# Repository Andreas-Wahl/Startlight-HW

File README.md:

# STARTAMPEL "Bären(n)keller" 🚦

## Project Overview 🏎️

In a private cellar bar that has been in existence for over two generations, originally named "Bärenkeller," a CARRERA® digital 132 racetrack was set up, and the first races were held. This quickly gained popularity among friends and acquaintances. As a result, the racetrack was gradually expanded, and possible extensions were discussed.

The idea of creating a custom starting light emerged because the original CARRERA® Startlight (30354) could not bridge three lanes (two lanes + pit lane). Additionally, the custom STARTAMPEL should not only display the start sequence with red lights but also indicate the race operation with green LEDs, the safety car/pace car operation, and a false start.

The idea was quickly taken up, the data signal was analyzed with an oscilloscope and data logger, and the development of hardware, software, and housing design was initiated.

In reference to the "Bärenkeller," which was renamed "Bären(n)keller" due to the expansion of the CARRERA® digital 132 racetrack, the custom starting light was also named "STARTAMPEL 'Bären(n)keller'."

The STARTAMPEL "Bären(n)keller" was so well received that the developer decided to produce a small quantity as "prototypes" and make the development available for non-commercial use.

## Licensing 📜

- **Electronics and Housing Design**: Released under the Creative Commons Attribution-NonCommercial-ShareAlike 4.0 International License (CC BY-NC-SA 4.0).
- **Software**: Released under the GNU Affero General Public License, Version 3.0 (AGPL-3.0).

## Repository Contents 📂

- **Schematic**: The complete schematic for the STARTAMPEL "Bären(n)keller".
- **PCB Layout**: The PCB layout files for the project.
- **Hardware Documentation**: Detailed documentation on the hardware development and usage.

## Getting Started 🚀

To get started with the project, clone the repository and follow the instructions in the documentation to set up the hardware and software.

```bash
git clone https://github.com/Andreas-Wahl/Startlight-HW.git

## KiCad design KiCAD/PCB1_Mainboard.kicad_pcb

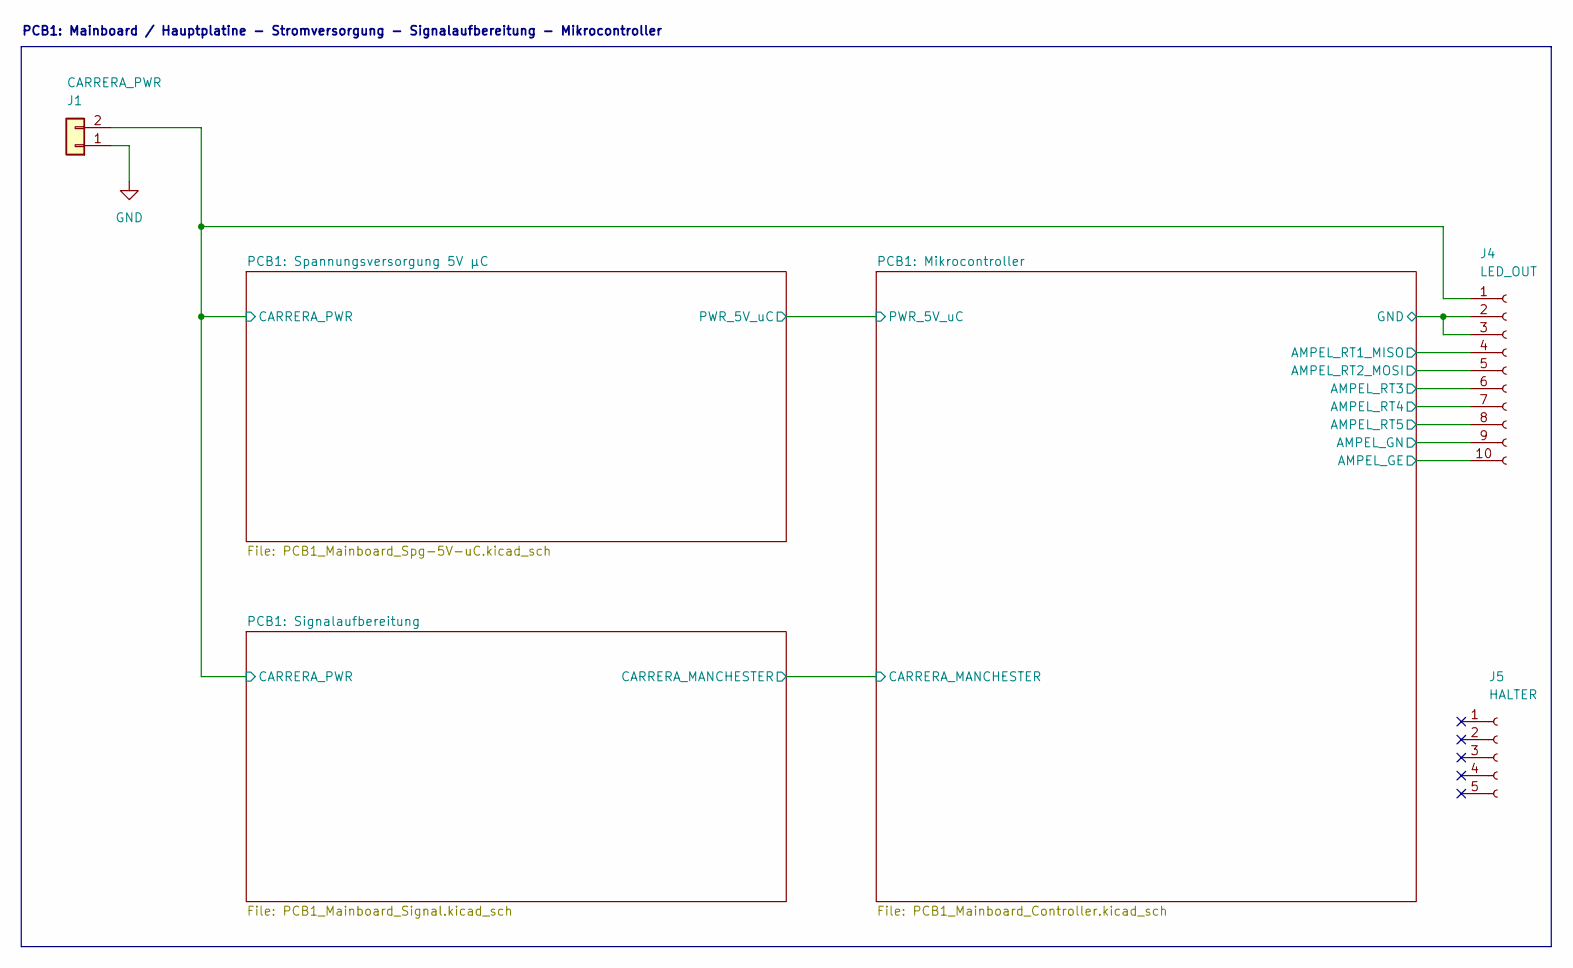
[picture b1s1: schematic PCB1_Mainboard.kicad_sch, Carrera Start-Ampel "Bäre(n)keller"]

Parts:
J1: CARRERA_PWR; JST_XH_B2B-XH-A_1x02_P2.50mm_Vertical
J4: LED_OUT; PinSocket_1x10_P2.54mm_Vertical
J5: HALTER; PinSocket_1x05_P2.54mm_Vertical

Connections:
/PCB1: Mikrocontroller/AMPEL_GE: J4.10; also elsewhere on the board
/PCB1: Mikrocontroller/AMPEL_GN: J4.9; also elsewhere on the board
/PCB1: Mikrocontroller/AMPEL_RT1_MISO: J4.4; also elsewhere on the board
/PCB1: Mikrocontroller/AMPEL_RT2_MOSI: J4.5; also elsewhere on the board
/PCB1: Mikrocontroller/AMPEL_RT3: J4.6; also elsewhere on the board
/PCB1: Mikrocontroller/AMPEL_RT4: J4.7; also elsewhere on the board
/PCB1: Mikrocontroller/AMPEL_RT5: J4.8; also elsewhere on the board
/PCB1: Signalaufbereitung/CARRERA_PWR: J1.2, J4.1; also elsewhere on the board
GND: J1.1, J4.2, J4.3; also elsewhere on the board

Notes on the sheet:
PCB1: Mainboard / Hauptplatine - Stromversorgung - Signalaufbereitung - Mikrocontroller

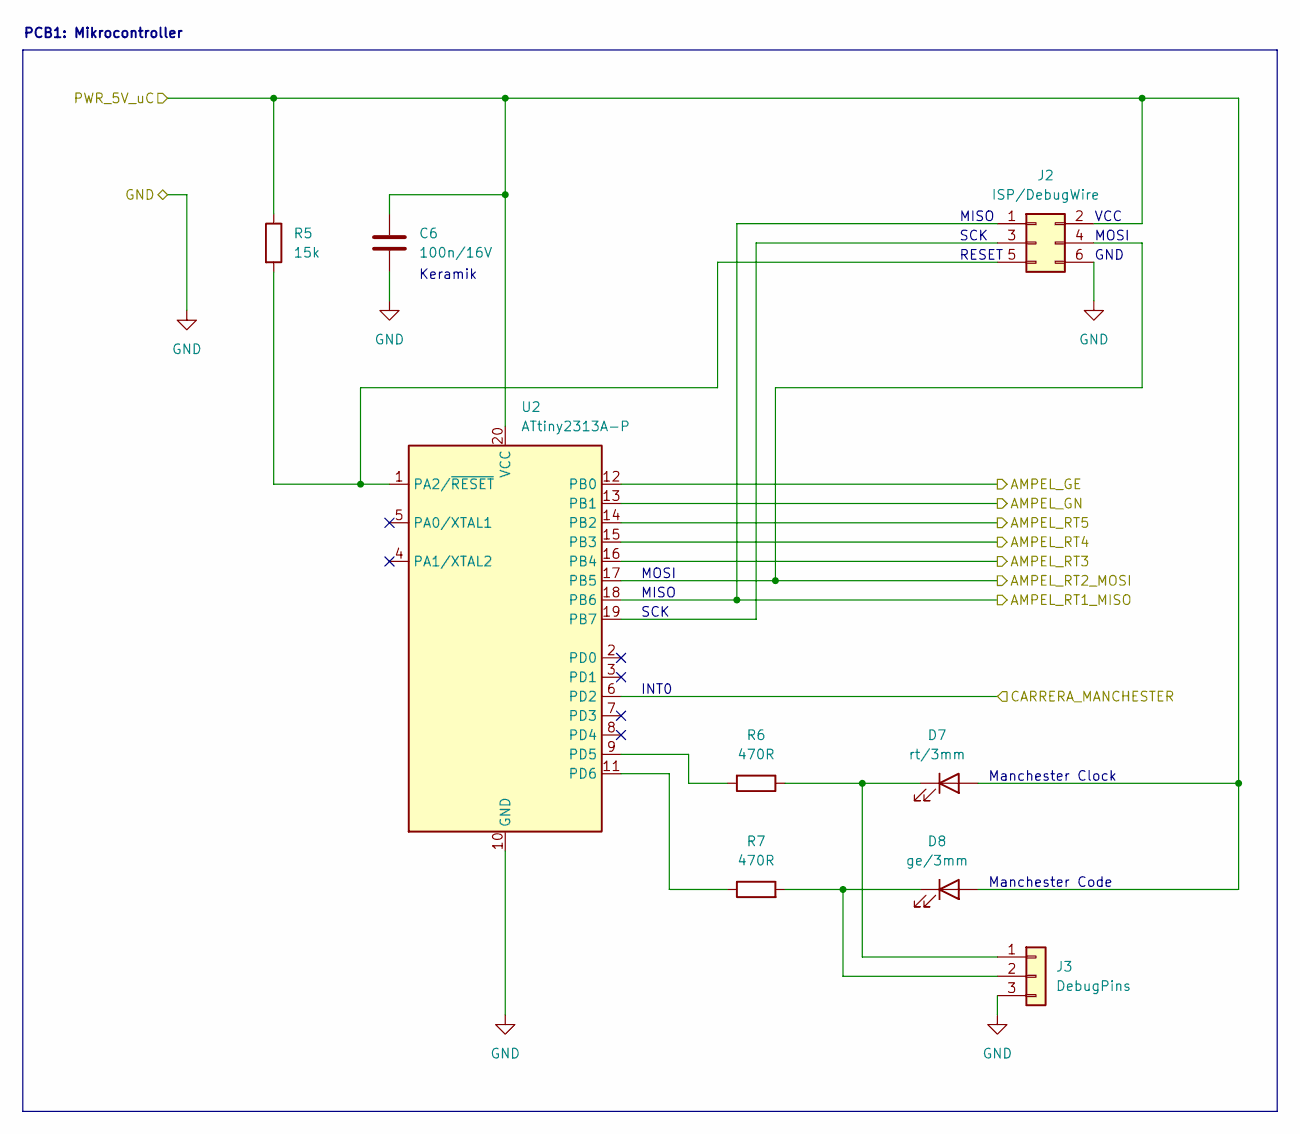
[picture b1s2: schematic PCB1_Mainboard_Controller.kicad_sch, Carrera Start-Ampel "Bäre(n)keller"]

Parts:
C6: 100n/16V; C_Disc_D5.0mm_W2.5mm_P5.00mm
D7: rt/3mm; LED_D3.0mm-rd
D8: ge/3mm; LED_D3.0mm-ye
J2: ISP/DebugWire; PinHeader_2x03_P2.54mm_Horizontal
J3: DebugPins; PinHeader_1x03_P2.54mm_Horizontal
R5: 15k; R_Axial_DIN0207_L6.3mm_D2.5mm_P10.16mm_Horizontal
R6, R7: 470R; R_Axial_DIN0207_L6.3mm_D2.5mm_P10.16mm_Horizontal
U2: ATtiny2313A-P; DIP-20_W7.62mm

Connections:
/PCB1: Mikrocontroller/AMPEL_GE: U2.12 (PB0); also elsewhere on the board
/PCB1: Mikrocontroller/AMPEL_GN: U2.13 (PB1); also elsewhere on the board
/PCB1: Mikrocontroller/AMPEL_RT1_MISO: J2.1, U2.18 (PB6); also elsewhere on the board
/PCB1: Mikrocontroller/AMPEL_RT2_MOSI: J2.4, U2.17 (PB5); also elsewhere on the board
/PCB1: Mikrocontroller/AMPEL_RT3: U2.16 (PB4); also elsewhere on the board
/PCB1: Mikrocontroller/AMPEL_RT4: U2.15 (PB3); also elsewhere on the board
/PCB1: Mikrocontroller/AMPEL_RT5: U2.14 (PB2); also elsewhere on the board
/PCB1: Mikrocontroller/CARRERA_MANCHESTER: U2.6 (PD2); also elsewhere on the board
/PCB1: Mikrocontroller/PWR_5V_uC: C6.1, D7.2 (A), D8.2 (A), J2.2, R5.1, U2.20 (VCC); also elsewhere on the board
GND: C6.2, J2.6, J3.3, U2.10 (GND); also elsewhere on the board
unnamed: D7.1 (K), J3.1, R6.1
unnamed: D8.1 (K), J3.2, R7.2
unnamed: J2.3, U2.19 (PB7)
unnamed: J2.5, R5.2, U2.1 (PA2/~RESET)
unnamed: R6.2, U2.9 (PD5)
unnamed: R7.1, U2.11 (PD6)

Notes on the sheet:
SCK
MISO
Manchester Clock
PCB1: Mikrocontroller
Keramik
GND
Manchester Code
MOSI
RESET
INT0
VCC

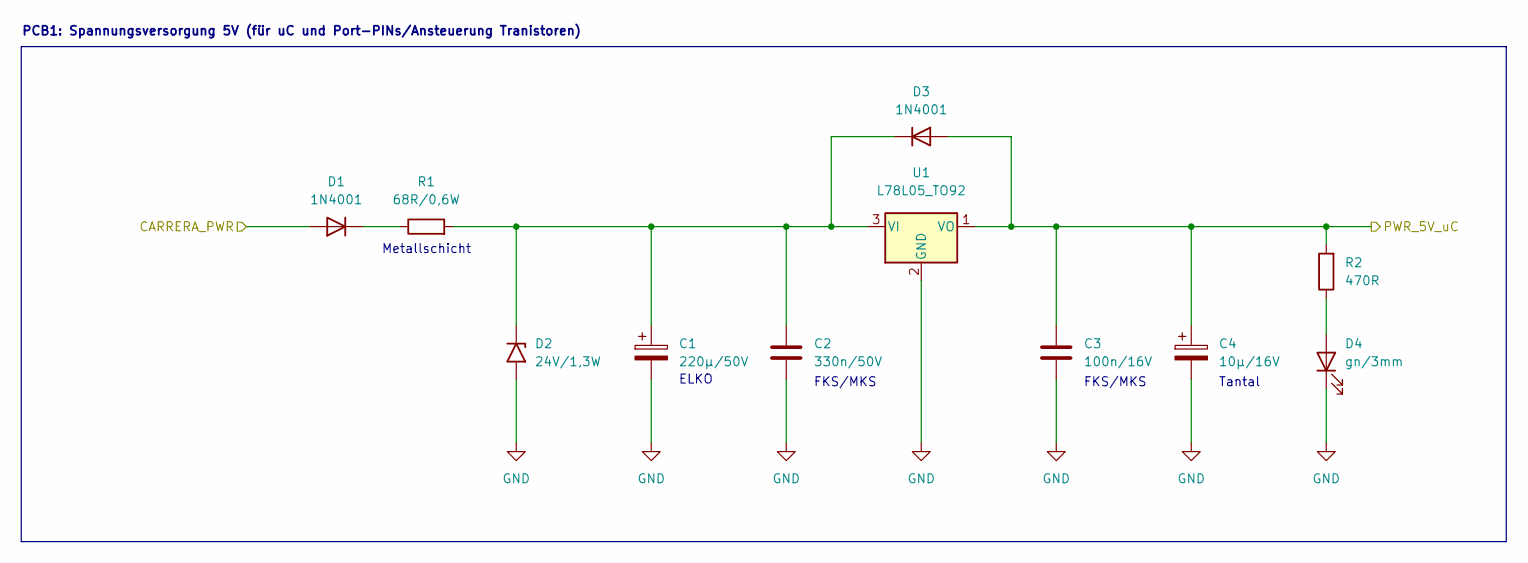
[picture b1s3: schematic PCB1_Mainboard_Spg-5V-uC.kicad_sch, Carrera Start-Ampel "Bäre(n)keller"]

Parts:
C1: 220µ/50V; CP_Radial_D10.0mm_P5.00mm
C2: 330n/50V; C_Rect_L7.2mm_W2.5mm_P5.00mm_FKS2_FKP2_MKS2_MKP2
C3: 100n/16V; C_Rect_L7.2mm_W2.5mm_P5.00mm_FKS2_FKP2_MKS2_MKP2
C4: 10µ/16V; CP_Radial_Tantal_D5.5mm_P2.50mm
D1, D3: 1N4001; D_DO-41_SOD81_P10.16mm_Horizontal
D2: 24V/1,3W; D_DO-41_SOD81_P10.16mm_Horizontal
D4: gn/3mm; LED_D3.0mm-gn
R1: 68R/0,6W; R_Axial_DIN0207_L6.3mm_D2.5mm_P10.16mm_Horizontal
R2: 470R; R_Axial_DIN0207_L6.3mm_D2.5mm_P10.16mm_Horizontal
U1: L78L05_TO92; TO-92_Wide

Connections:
/PCB1: Mikrocontroller/PWR_5V_uC: C3.1, C4.1, D3.2 (A), R2.2, U1.1 (VO); also elsewhere on the board
/PCB1: Signalaufbereitung/CARRERA_PWR: D1.2 (A); also elsewhere on the board
GND: C1.2, C2.2, C3.2, C4.2, D2.2 (A2), D4.1 (K), U1.2 (GND); also elsewhere on the board
unnamed: D1.1 (K), R1.1
unnamed: C1.1, C2.1, D2.1 (A1), D3.1 (K), R1.2, U1.3 (VI)
unnamed: D4.2 (A), R2.1

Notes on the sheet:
Tantal
Metallschicht
ELKO
PCB1: Spannungsversorgung 5V (für uC und Port-PINs/Ansteuerung Tranistoren)
FKS/MKS

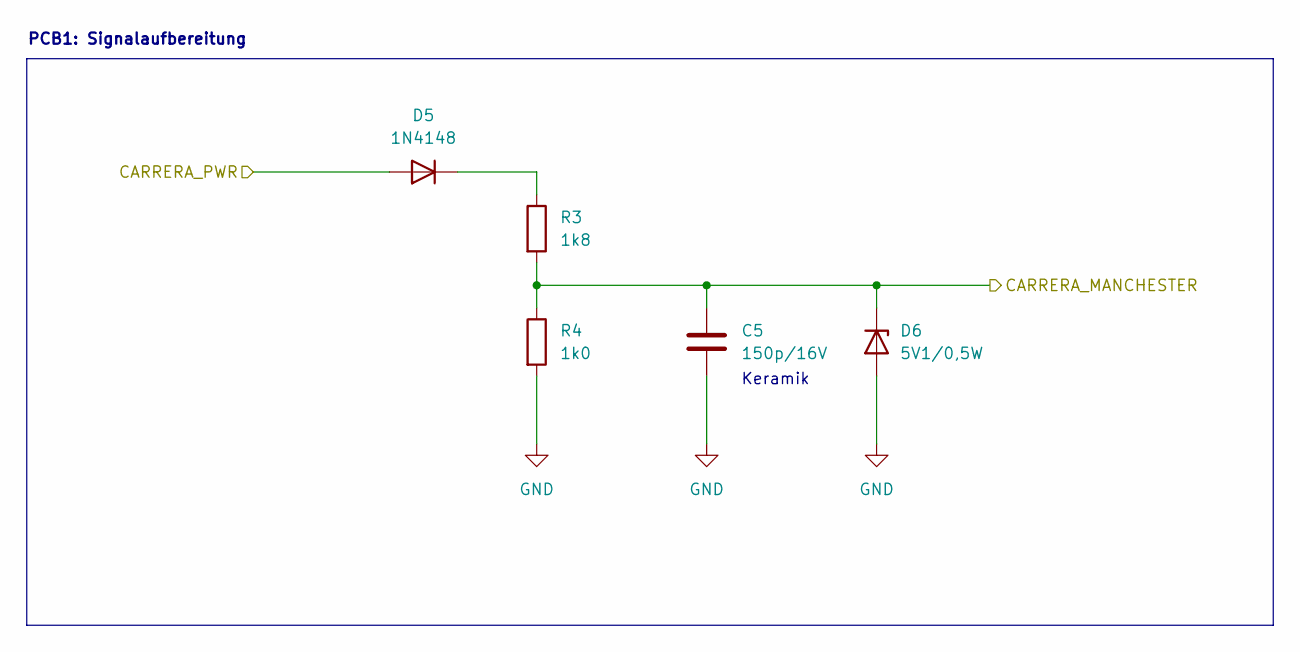
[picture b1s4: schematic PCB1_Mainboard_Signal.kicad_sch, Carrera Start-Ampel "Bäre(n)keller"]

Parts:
C5: 150p/16V; C_Disc_D5.0mm_W2.5mm_P5.00mm
D5: 1N4148; D_DO-35_SOD27_P10.16mm_Horizontal
D6: 5V1/0,5W; D_DO-35_SOD27_P10.16mm_Horizontal
R3: 1k8; R_Axial_DIN0207_L6.3mm_D2.5mm_P10.16mm_Horizontal
R4: 1k0; R_Axial_DIN0207_L6.3mm_D2.5mm_P10.16mm_Horizontal

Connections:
/PCB1: Mikrocontroller/CARRERA_MANCHESTER: C5.1, D6.1 (K), R3.2, R4.1; also elsewhere on the board
/PCB1: Signalaufbereitung/CARRERA_PWR: D5.2 (A); also elsewhere on the board
GND: C5.2, D6.2 (A), R4.2; also elsewhere on the board
unnamed: D5.1 (K), R3.1

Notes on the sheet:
PCB1: Signalaufbereitung
Keramik

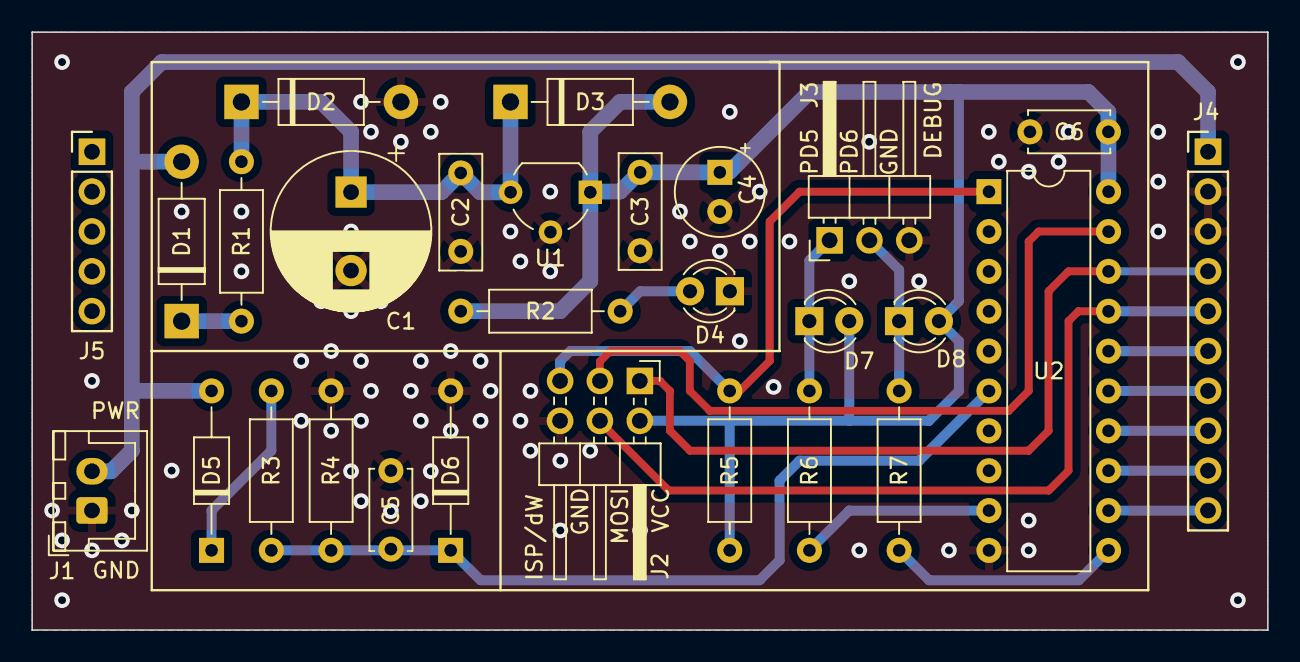
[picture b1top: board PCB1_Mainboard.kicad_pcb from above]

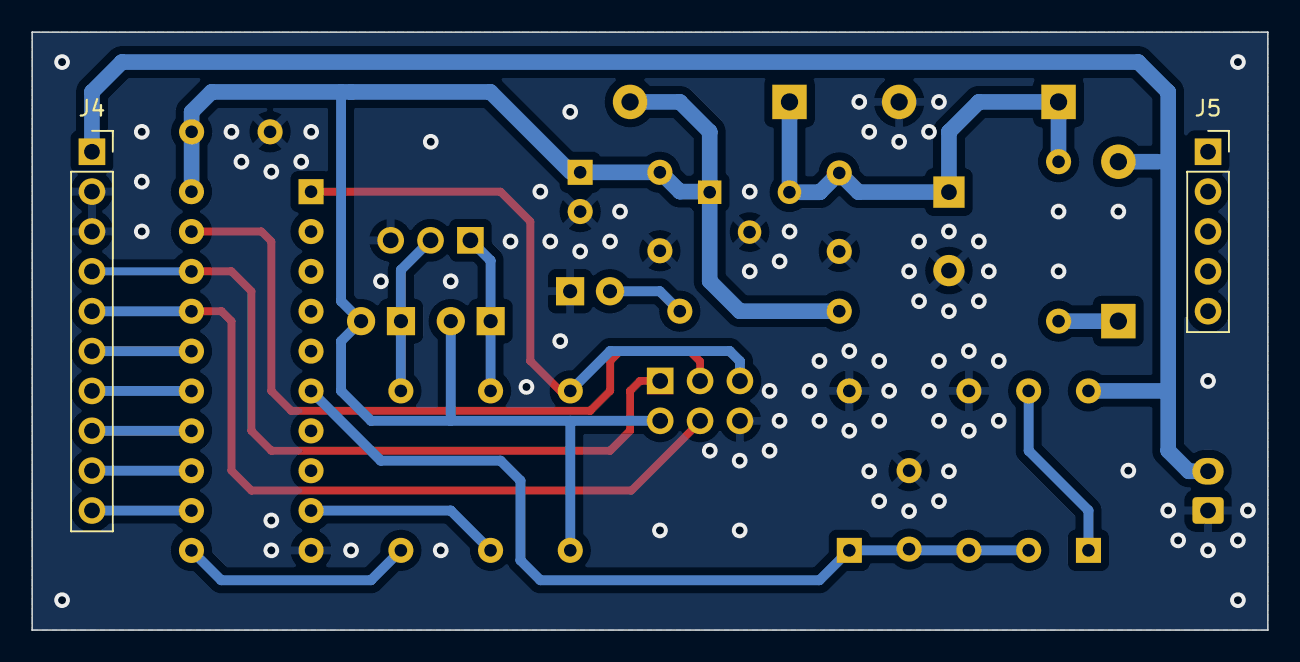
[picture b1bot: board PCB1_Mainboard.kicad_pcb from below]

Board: 2 copper layers, 78.7 x 38.1 mm, 28 parts (2 on the bottom side), 21 nets.

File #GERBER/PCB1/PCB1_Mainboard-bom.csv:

Designator,Quantity,Value,Footprint,Package,MPN,DNP,Mount_Type,Sim.Device,Sim.Pins
C1,1,220µ/50V,CP_Radial_D10.0mm_P5.00mm,,,,tht,,
C2,1,330n/50V,C_Rect_L7.2mm_W2.5mm_P5.00mm_FKS2_FKP2_MKS2_MKP2,,,,tht,,
C3,1,100n/16V,C_Rect_L7.2mm_W2.5mm_P5.00mm_FKS2_FKP2_MKS2_MKP2,,,,tht,,
C4,1,10µ/16V,CP_Radial_Tantal_D5.5mm_P2.50mm,,,,tht,,
C5,1,150p/16V,C_Disc_D5.0mm_W2.5mm_P5.00mm,,,,tht,,
C6,1,100n/16V,C_Disc_D5.0mm_W2.5mm_P5.00mm,,,,tht,,
"D1, D3",2,1N4001,D_DO-41_SOD81_P10.16mm_Horizontal,,,,tht,D,1=K 2=A
D2,1,"24V/1,3W",D_DO-41_SOD81_P10.16mm_Horizontal,,,,tht,,
D4,1,gn/3mm,LED_D3.0mm-gn,,,,tht,,
D5,1,1N4148,D_DO-35_SOD27_P10.16mm_Horizontal,,,,tht,D,1=K 2=A
D6,1,"5V1/0,5W",D_DO-35_SOD27_P10.16mm_Horizontal,,,,tht,,
D7,1,rt/3mm,LED_D3.0mm-rd,,,,tht,,
D8,1,ge/3mm,LED_D3.0mm-ye,,,,tht,,
J1,1,CARRERA_PWR,JST_XH_B2B-XH-A_1x02_P2.50mm_Vertical,,,,tht,,
J2,1,ISP/DebugWire,PinHeader_2x03_P2.54mm_Horizontal,,,,tht,,
J3,1,DebugPins,PinHeader_1x03_P2.54mm_Horizontal,,,,tht,,
J4,1,LED_OUT,PinSocket_1x10_P2.54mm_Vertical,,,,tht,,
J5,1,HALTER,PinSocket_1x05_P2.54mm_Vertical,,,,tht,,
R1,1,"68R/0,6W",R_Axial_DIN0207_L6.3mm_D2.5mm_P10.16mm_Horizontal,,,,tht,,
"R2, R6, R7",3,470R,R_Axial_DIN0207_L6.3mm_D2.5mm_P10.16mm_Horizontal,,,,tht,,
R3,1,1k8,R_Axial_DIN0207_L6.3mm_D2.5mm_P10.16mm_Horizontal,,,,tht,,
R4,1,1k0,R_Axial_DIN0207_L6.3mm_D2.5mm_P10.16mm_Horizontal,,,,tht,,
R5,1,15k,R_Axial_DIN0207_L6.3mm_D2.5mm_P10.16mm_Horizontal,,,,tht,,
U1,1,L78L05_TO92,TO-92_Wide,,,,tht,,
U2,1,ATtiny2313A-P,DIP-20_W7.62mm,,,,tht,,

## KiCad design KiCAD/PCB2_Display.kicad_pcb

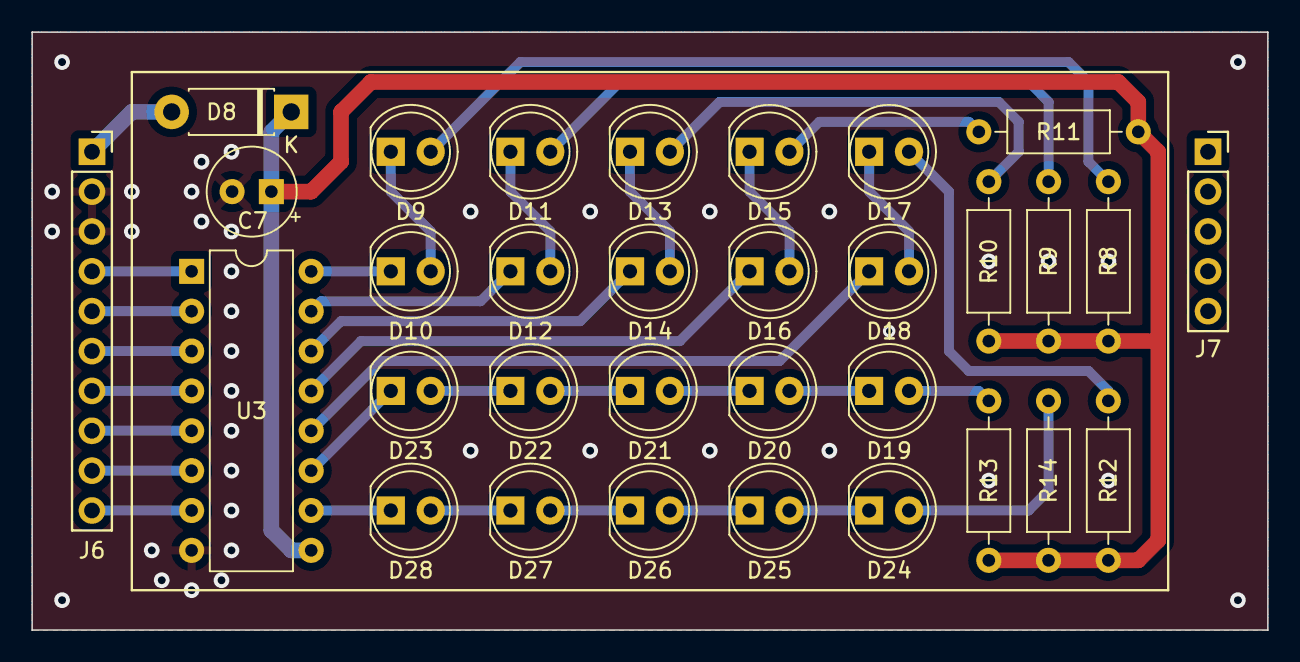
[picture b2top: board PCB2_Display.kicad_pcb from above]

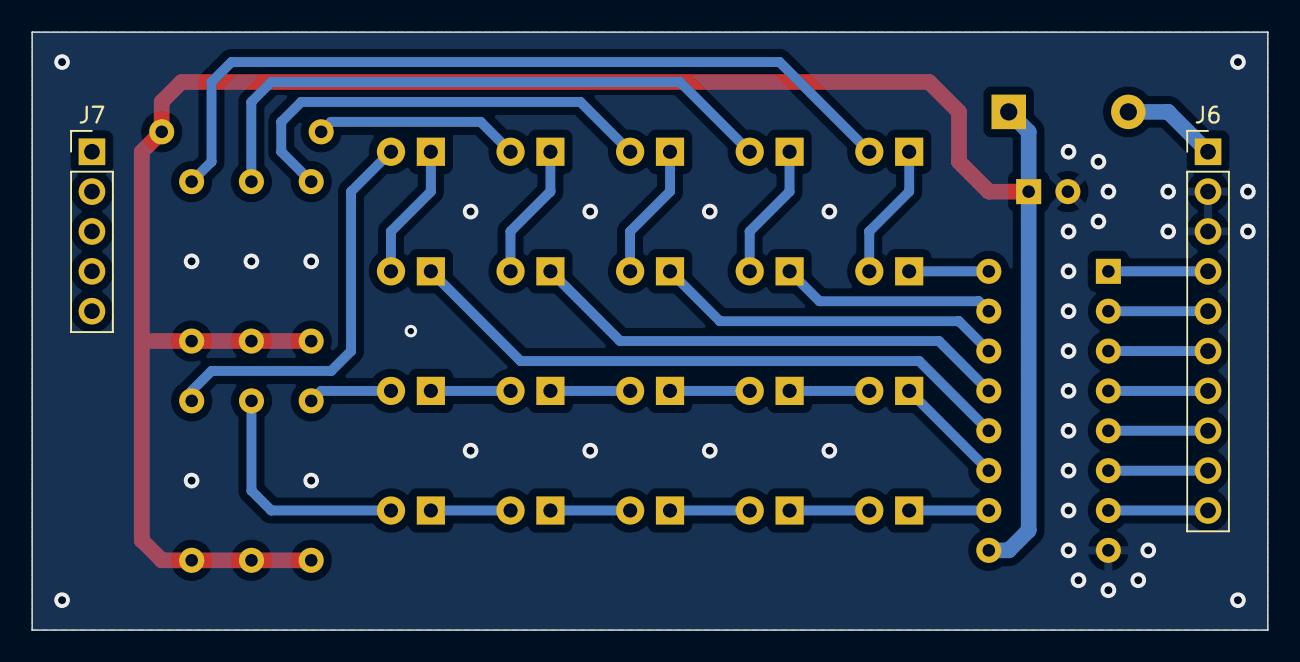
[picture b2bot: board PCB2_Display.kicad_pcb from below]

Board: 2 copper layers, 78.7 x 38.1 mm, 32 parts (2 on the bottom side), 37 nets.

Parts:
C7: 10uF/50V; CP_Radial_Tantal_D5.5mm_P2.50mm
D8: 1N4001; D_DO-41_SOD81_P7.62mm_Horizontal
D9, D10, D11, D12, D13, D14, D15, D16, D17, D18: rt/5mm; LED_D5.0mm_rd
D19, D20, D21, D22, D23: gn/5mm; LED_D5.0mm_gn
D24, D25, D26, D27, D28: ge/5mm; LED_D5.0mm_ye
J6: LED_IN; PinHeader_1x10_P2.54mm_Vertical
J7: HALTER; PinHeader_1x05_P2.54mm_Vertical
R8, R9, R10, R11, R12: 560R; R_Axial_DIN0207_L6.3mm_D2.5mm_P10.16mm_Horizontal
R13, R14: 220R; R_Axial_DIN0207_L6.3mm_D2.5mm_P10.16mm_Horizontal
U3: ULN2003A; DIP-16_W7.62mm

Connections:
GND: C7.2, J6.2, J6.3, U3.8 (GND)
unnamed: D8.2 (A), J6.1
unnamed: C7.1, D8.1 (K), R8.1, R9.1, R10.1, R11.1, R12.1, R13.2, R14.2, U3.9 (COM)
unnamed: D9.2 (A), R8.2
unnamed: D9.1 (K), D10.2 (A)
unnamed: D10.1 (K), U3.16 (O1)
unnamed: D11.2 (A), R9.2
unnamed: D11.1 (K), D12.2 (A)
unnamed: D12.1 (K), U3.15 (O2)
unnamed: D13.2 (A), R10.2
unnamed: D13.1 (K), D14.2 (A)
unnamed: D14.1 (K), U3.14 (O3)
unnamed: D15.2 (A), R11.2
unnamed: D15.1 (K), D16.2 (A)
unnamed: D16.1 (K), U3.13 (O4)
unnamed: D17.2 (A), R12.2
unnamed: D17.1 (K), D18.2 (A)
unnamed: D18.1 (K), U3.12 (O5)
unnamed: D19.2 (A), R13.1
unnamed: D19.1 (K), D20.2 (A)
unnamed: D20.1 (K), D21.2 (A)
unnamed: D21.1 (K), D22.2 (A)
unnamed: D22.1 (K), D23.2 (A)
unnamed: D23.1 (K), U3.11 (O6)
unnamed: D24.2 (A), R14.1
unnamed: D24.1 (K), D25.2 (A)
unnamed: D25.1 (K), D26.2 (A)
unnamed: D26.1 (K), D27.2 (A)
unnamed: D27.1 (K), D28.2 (A)
unnamed: D28.1 (K), U3.10 (O7)
unnamed: J6.4, U3.1 (I1)
unnamed: J6.5, U3.2 (I2)
unnamed: J6.6, U3.3 (I3)
unnamed: J6.7, U3.4 (I4)
unnamed: J6.8, U3.5 (I5)
unnamed: J6.9, U3.6 (I6)
unnamed: J6.10, U3.7 (I7)

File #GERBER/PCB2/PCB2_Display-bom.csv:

Designator,Quantity,Value,Footprint,Package,MPN,DNP,Mount_Type,Description,Sim.Device,Sim.Pins
C7,1,10uF/50V,CP_Radial_Tantal_D5.5mm_P2.50mm,,,,tht,Polarized capacitor,,
"D10, D11, D12, D13, D14, D15, D16, D17, D18, D9",10,rt/5mm,LED_D5.0mm_rd,,,,tht,Light emitting diode,,
"D19, D20, D21, D22, D23",5,gn/5mm,LED_D5.0mm_gn,,,,tht,Light emitting diode,,
"D24, D25, D26, D27, D28",5,ge/5mm,LED_D5.0mm_ye,,,,tht,Light emitting diode,,
D8,1,1N4001,D_DO-41_SOD81_P7.62mm_Horizontal,,,,tht,"50V 1A General Purpose Rectifier Diode, DO-41",D,1=K 2=A
J6,1,LED_IN,PinHeader_1x10_P2.54mm_Vertical,,,,tht,"Generic connector, single row, 01x10, script generated",,
J7,1,HALTER,PinHeader_1x05_P2.54mm_Vertical,,,,tht,"Generic connector, single row, 01x05, script generated",,
"R10, R11, R12, R8, R9",5,560R,R_Axial_DIN0207_L6.3mm_D2.5mm_P10.16mm_Horizontal,,,,tht,Resistor,,
"R13, R14",2,220R,R_Axial_DIN0207_L6.3mm_D2.5mm_P10.16mm_Horizontal,,,,tht,Resistor,,
U3,1,ULN2003A,DIP-16_W7.62mm,,,,tht,"High Voltage, High Current Darlington Transistor Arrays, SOIC16/SOIC16W/DIP16/TSSOP16",,

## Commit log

2024-12-15 Create LICENSE

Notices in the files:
KiCAD/PCB1_Mainboard.kicad_sch:
LICENSE: Attribution-NonCommercial-NoDerivatives 4.0 International (CC BY-NC-ND 4.0)
